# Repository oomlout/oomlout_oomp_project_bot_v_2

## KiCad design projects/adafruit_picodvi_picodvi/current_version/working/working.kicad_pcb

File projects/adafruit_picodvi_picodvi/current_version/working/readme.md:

# picodvi
 
## summary 
* id: adafruit_picodvi_picodvi
* user: adafruit
* name: picodvi
* board: picodvi
* repo: https://github.com/adafruit/PicoDVI
* src_file_repo_kicad_pcb: hardware/mini_board/picodvi.kicad_pcb
* src_file_repo_kicad_pcb_link: https://github.com/adafruit/PicoDVI/tree/master/hardware/mini_board/picodvi.kicad_pcb
* src_file_repo_kicad_sch: hardware/mini_board/picodvi.kicad_sch
* src_file_repo_kicad_sch_link: https://github.com/adafruit/PicoDVI/tree/master/hardware/mini_board/picodvi.kicad_sch

* src_file_repo_sch: hardware/mini_board/picodvi.sch
* src_file_repo_sch_link: https://github.com/adafruit/PicoDVI/tree/master/hardware/mini_board/picodvi.sch
* full details link: https://github.com/oomlout/oomlout_oomp_project_bot_v_2/tree/main/projects/adafruit_picodvi_picodvi/current_version/working  

## schematic  
  
[schematic (pdf)](working_schematic.pdf) 

## pcb  

[board (pdf)](working.pdf)  

## working_bom
| Id | Designator | Footprint | Quantity | Designation | Supplier and ref |  | None | 
| --- | --- | --- | --- | --- | --- | --- | --- | 
| 1 | R6,R1,R2 | R_0402_1005Metric | 3 | 2k2 |  |  | [''] | 
| 2 | D1 | LED_0805_2012Metric | 1 | LED |  |  | [''] | 
| 3 | J5 | HDMI-SS-53000 | 1 | NOT_HDMI_A |  |  | [''] | 
| 4 | TP1 | TestPoint_Pad_1.0x1.0mm | 1 | TestPoint |  |  | [''] | 
| 5 | J1 | USB_A_PLUG_PCB | 1 | USB_A |  |  | [''] | 
| 6 | U1 | QFN-56_EP_7x7_Pitch0.4mm | 1 | RP2040 |  |  | [''] | 
| 7 | C13,C6,C2,C8,C9,C5,C4 | C_0402_1005Metric | 7 | 100n |  |  | [''] | 
| 8 | R3,R12,R18,R17,R16,R19,R15,R13,R14 | R_0402_1005Metric | 9 | 270 |  |  | [''] | 
| 9 | C7,C3,C11,C1 | C_0402_1005Metric | 4 | 1u |  |  | [''] | 
| 10 | SW2,SW1 | SW_SPST_PTS815 | 2 | SW_Push |  |  | [''] | 
| 11 | Y1 | Crystal_SMD_3225-4Pin_3.2x2.5mm | 1 | 12 M |  |  | [''] | 
| 12 | R4,R5 | R_0402_1005Metric | 2 | 27R |  |  | [''] | 
| 13 | U2 | SOT-23-5_HandSoldering | 1 | NCP115ASN330 |  |  | [''] | 
| 14 | C10,C12 | C_0402_1005Metric | 2 | 10p |  |  | [''] | 
| 15 | U3 | WSON-8-1EP_6x5mm_P1.27mm_EP3.4x4mm | 1 | W25Q16JV |  |  | [''] | 

## bom_schematic
| Ref | Qnty | Value | Cmp name | Footprint | Description | Vendor | DNP | 
| --- | --- | --- | --- | --- | --- | --- | --- | 
| C1, C3, C7, C11, C22, C23, C24 | 7 | 1u | C | Capacitor_SMD:C_0402_1005Metric | Unpolarized capacitor |  |  | 
| C2, C4, C5, C6, C8, C9, C13 | 7 | 100n | C | Capacitor_SMD:C_0402_1005Metric | Unpolarized capacitor |  |  | 
| C10, C12 | 2 | 10p | C | Capacitor_SMD:C_0402_1005Metric | Unpolarized capacitor |  |  | 
| D1, D2 | 2 | LED | LED | LED_SMD:LED_0805_2012Metric | Light emitting diode |  |  | 
| J1 | 1 | USB_OTG | USB_OTG-Connector | Connector_USB:USB_Micro-B_Molex-105017-0001 |  |  |  | 
| J2 | 1 | Conn_01x05 | Conn_01x05 | picodvi:PinHeader_1x05_P2.54mm_Vertical | Generic connector, single row, 01x05, script generated (kicad-library-utils/schlib/autogen/connector/) |  |  | 
| J3, J4 | 2 | 02x06 | Conn_02x06_Odd_Even | picodvi:PinHeader_2x06_P2.54mm_Horizontal | Generic connector, double row, 02x06, odd/even pin numbering scheme (row 1 odd numbers, row 2 even numbers), script generated (kicad-library-utils/schlib/autogen/connector/) |  |  | 
| J5 | 1 | NOT_HDMI_A | HDMI_A | picodvi:HDMI-SS-53000 | HDMI type A connector |  |  | 
| J6 | 1 | Conn_01x02 | Conn_01x02 | Connector_PinHeader_2.54mm:PinHeader_1x02_P2.54mm_Vertical | Generic connector, single row, 01x02, script generated (kicad-library-utils/schlib/autogen/connector/) |  |  | 
| R1, R3, R6, R7, R8, R9, R11, R20 | 8 | 2k2 | R | Resistor_SMD:R_0402_1005Metric | Resistor |  |  | 
| R2 | 1 | DNF | R | Resistor_SMD:R_0402_1005Metric | Resistor |  |  | 
| R4, R5 | 2 | 27R | R | Resistor_SMD:R_0402_1005Metric | Resistor |  |  | 
| R10, R12, R13, R14, R15, R16, R17, R18, R19 | 9 | 270 | R | Resistor_SMD:R_0402_1005Metric | Resistor |  |  | 
| SW1, SW2, SW3 | 3 | SW_Push | SW_Push | picodvi:SW_SPST_PTS815 | Push button switch, generic, two pins |  |  | 
| U1 | 1 | RP2040 | Pico2040 | picodvi:QFN-56_EP_7x7_Pitch0.4mm |  |  |  | 
| U2 | 1 | NCP115ASN330 | NCP115ASN330 | Package_TO_SOT_SMD:SOT-23-5_HandSoldering |  |  |  | 
| U3 | 1 | W25Q16JV | AT25SF081-XMHD-X-Memory_Flash | Package_SON:WSON-8-1EP_6x5mm_P1.27mm_EP3.4x4mm |  |  |  | 
| Y1 | 1 | 12 M | Crystal_GND24 | Crystal:Crystal_SMD_3225-4Pin_3.2x2.5mm | Four pin crystal, GND on pins 2 and 4 |  |  |

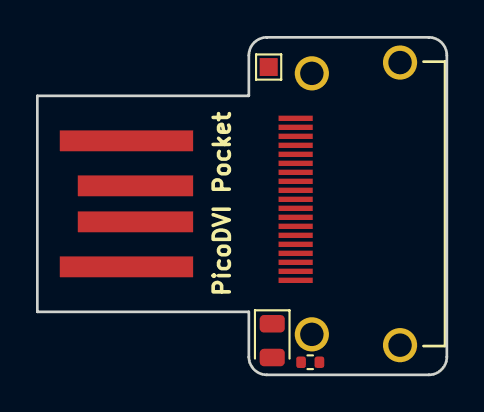
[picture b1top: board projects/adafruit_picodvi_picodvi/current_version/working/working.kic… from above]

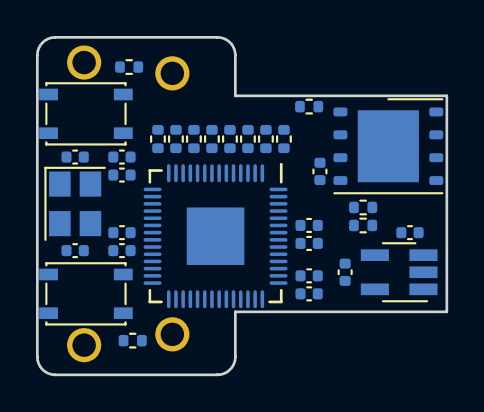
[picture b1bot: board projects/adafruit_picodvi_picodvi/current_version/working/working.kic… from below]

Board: 4 copper layers, 22.8 x 18.8 mm, 37 parts (32 on the bottom side), 37 nets, no tracks yet.

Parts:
C1, C3, C7, C11: 1u; C_0402_1005Metric
C2, C4, C5, C6, C8, C9, C13: 100n; C_0402_1005Metric
C10, C12: 10p; C_0402_1005Metric
D1: LED; LED_0805_2012Metric
J1: USB_A; USB_A_PLUG_PCB
J5: NOT_HDMI_A; HDMI-SS-53000
R1, R2, R6: 2k2; R_0402_1005Metric
R3, R12, R13, R14, R15, R16, R17, R18, R19: 270; R_0402_1005Metric
R4, R5: 27R; R_0402_1005Metric
SW1, SW2: SW_Push; SW_SPST_PTS815
TP1: TestPoint; TestPoint_Pad_1.0x1.0mm
U1: RP2040; QFN-56_EP_7x7_Pitch0.4mm
U2: NCP115ASN330; SOT-23-5_HandSoldering
U3: W25Q16JV; WSON-8-1EP_6x5mm_P1.27mm_EP3.4x4mm
Y1: 12 M; Crystal_SMD_3225-4Pin_3.2x2.5mm

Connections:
+1V1: C3.1, C5.1, C8.1, U1.23 (DVDD), U1.45 (LDO_VOUT), U1.50 (DVDD)
+3V3: C1.1, C2.1, C4.1, C6.1, C9.1, C11.1, C13.1, R1.1, R2.1, U1.1 (IOVDD), U1.10 (IOVDD), U1.22 (IOVDD), U1.33 (IOVDD), U1.42 (IOVDD), U1.43 (ADC_IOVDD), U1.44 (LDO_IOVDD), U1.48 (USB_IOVDD), U1.49 (IOVDD), U2.5 (OUT), U3.8 (VCC)
/DVI_CK+: J5.10 (CK+), R15.1
/DVI_CK-: J5.12 (CK-), R19.1
/DVI_D0+: J5.7 (D0+), R14.1
/DVI_D0-: J5.9 (D0-), R18.1
/DVI_D1+: J5.4 (D1+), R13.1
/DVI_D1-: J5.6 (D1-), R17.1
/DVI_D2+: J5.1 (D2+), R12.1
/DVI_D2-: J5.3 (D2-), R16.1
/FLASH_SCK: U1.52 (QSPI_SCK), U3.6 (SCK)
/FLASH_SD0: U1.53 (QSPI_SD0), U3.5 (SI/IO0)
/FLASH_SD1: U1.55 (QSPI_SD1), U3.2 (SO/IO1)
/FLASH_SD2: U1.54 (QSPI_SD2), U3.3 (~WP~/IO2)
/FLASH_SD3: U1.51 (QSPI_SD3), U3.7 (~HOLD~/IO3)
/FLASH_~CS: R3.1, U1.56 (~QSPI_SS~), U3.1 (~CS)
/RUN_~RST: R1.2, SW1.2, U1.26 (RUN/~RST~)
/SPARE_IO: TP1.1, U1.40 (ADC2/GPIO28)
/USB_D+: J1.3 (D+), R5.1
/USB_D-: J1.2 (D-), R4.1
/USB_DX+: R5.2, U1.47 (USB_DP)
/USB_DX-: R4.2, U1.46 (USB_DM)
/USER_LED: R6.1, U1.18 (GPIO15), U1.39 (ADC1/GPIO27)
/XIN: C12.1, U1.20 (XIN), Y1.3
/XOUT: C10.1, U1.21 (XOUT), Y1.1
/uC_DVI_CK+: R15.2, U1.7 (GPIO5)
/uC_DVI_CK-: R19.2, U1.6 (GPIO4)
/uC_DVI_D0+: R14.2, U1.9 (GPIO7)
/uC_DVI_D0-: R18.2, U1.8 (GPIO6)
/uC_DVI_D1+: R13.2, U1.12 (GPIO9)
/uC_DVI_D1-: R17.2, U1.11 (GPIO8)
/uC_DVI_D2+: R12.2, U1.14 (GPIO11)
/uC_DVI_D2-: R16.2, U1.13 (GPIO10)
/~USER_BUTTON: R2.2, R3.2, SW2.2, U1.17 (GPIO14)
GND: C1.2, C2.2, C3.2, C4.2, C5.2, C6.2, C7.2, C8.2, C9.2, C10.2, C11.2, C12.2, C13.2, D1.1 (K), J1.4 (GND), J5.2 (D2S), J5.5 (D1S), J5.8 (D0S), J5.11 (CKS), J5.17 (GND), J5.SH, SW1.1, SW2.1, U1.0 (GND), U1.19 (TESTEN), U2.2 (GND), U3.4 (GND), Y1.2, Y1.4
unnamed: D1.2 (A), R6.2
VBUS: C7.1, J1.1 (VBUS), J5.18 (+5V), U2.1 (IN), U2.3 (EN)

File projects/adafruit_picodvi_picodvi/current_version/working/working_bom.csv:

"Id";"Designator";"Footprint";"Quantity";"Designation";"Supplier and ref";
1;"R6,R1,R2";"R_0402_1005Metric";3;"2k2";;;
2;"D1";"LED_0805_2012Metric";1;"LED";;;
3;"J5";"HDMI-SS-53000";1;"NOT_HDMI_A";;;
4;"TP1";"TestPoint_Pad_1.0x1.0mm";1;"TestPoint";;;
5;"J1";"USB_A_PLUG_PCB";1;"USB_A";;;
6;"U1";"QFN-56_EP_7x7_Pitch0.4mm";1;"RP2040";;;
7;"C13,C6,C2,C8,C9,C5,C4";"C_0402_1005Metric";7;"100n";;;
8;"R3,R12,R18,R17,R16,R19,R15,R13,R14";"R_0402_1005Metric";9;"270";;;
9;"C7,C3,C11,C1";"C_0402_1005Metric";4;"1u";;;
10;"SW2,SW1";"SW_SPST_PTS815";2;"SW_Push";;;
11;"Y1";"Crystal_SMD_3225-4Pin_3.2x2.5mm";1;"12 M";;;
12;"R4,R5";"R_0402_1005Metric";2;"27R";;;
13;"U2";"SOT-23-5_HandSoldering";1;"NCP115ASN330";;;
14;"C10,C12";"C_0402_1005Metric";2;"10p";;;
15;"U3";"WSON-8-1EP_6x5mm_P1.27mm_EP3.4x4mm";1;"W25Q16JV";;;

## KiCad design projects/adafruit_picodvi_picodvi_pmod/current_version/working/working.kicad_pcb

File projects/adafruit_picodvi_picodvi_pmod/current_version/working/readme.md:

# picodvi
 
## summary 
* id: adafruit_picodvi_picodvi_pmod
* user: adafruit
* name: picodvi
* board: picodvi_pmod
* repo: https://github.com/adafruit/PicoDVI
* src_file_repo_kicad_pcb: hardware/pmod_hdmi/picodvi_pmod.kicad_pcb
* src_file_repo_kicad_pcb_link: https://github.com/adafruit/PicoDVI/tree/master/hardware/pmod_hdmi/picodvi_pmod.kicad_pcb
* src_file_repo_kicad_sch: hardware/mini_board/picodvi.kicad_sch
* src_file_repo_kicad_sch_link: https://github.com/adafruit/PicoDVI/tree/master/hardware/mini_board/picodvi.kicad_sch

* src_file_repo_sch: hardware/pmod_hdmi/picodvi_pmod.sch
* src_file_repo_sch_link: https://github.com/adafruit/PicoDVI/tree/master/hardware/pmod_hdmi/picodvi_pmod.sch
* full details link: https://github.com/oomlout/oomlout_oomp_project_bot_v_2/tree/main/projects/adafruit_picodvi_picodvi_pmod/current_version/working  

## schematic  
  
[schematic (pdf)](working_schematic.pdf) 

## pcb  

[board (pdf)](working.pdf)  

## working_bom
| Id | Designator | Footprint | Quantity | Designation | Supplier and ref |  | None | 
| --- | --- | --- | --- | --- | --- | --- | --- | 
| 1 | C2,C3,C4,C5,C6,C7,C8,C9,C1 | C_0402_1005Metric | 9 | 220n |  |  | [''] | 
| 2 | J2 | PinHeader_1x02_P2.54mm_Vertical | 1 | Conn_01x02 |  |  | [''] | 
| 3 | J1 | PinSocket_2x06_P2.54mm_Horizontal | 1 | 02x06 |  |  | [''] | 
| 4 | J3 | HDMI-SS-53000 | 1 | HDMI_A |  |  | [''] | 

## bom_schematic
| Ref | Qnty | Value | Cmp name | Footprint | Description | Vendor | DNP | 
| --- | --- | --- | --- | --- | --- | --- | --- | 
| C1, C2, C3, C4, C5, C6, C7, C8, C9 | 9 | 220n | C | Capacitor_SMD:C_0402_1005Metric | Unpolarized capacitor |  |  | 
| J1 | 1 | 02x06 | Conn_02x06_Odd_Even | Connector_PinSocket_2.54mm:PinSocket_2x06_P2.54mm_Horizontal | Generic connector, double row, 02x06, odd/even pin numbering scheme (row 1 odd numbers, row 2 even numbers), script generated (kicad-library-utils/schlib/autogen/connector/) |  |  | 
| J2 | 1 | Conn_01x02 | Conn_01x02 | Connector_PinHeader_2.54mm:PinHeader_1x02_P2.54mm_Vertical | Generic connector, single row, 01x02, script generated (kicad-library-utils/schlib/autogen/connector/) |  |  | 
| J3 | 1 | HDMI_A | HDMI_A | picodvi:HDMI-SS-53000 | HDMI type A connector |  |  |

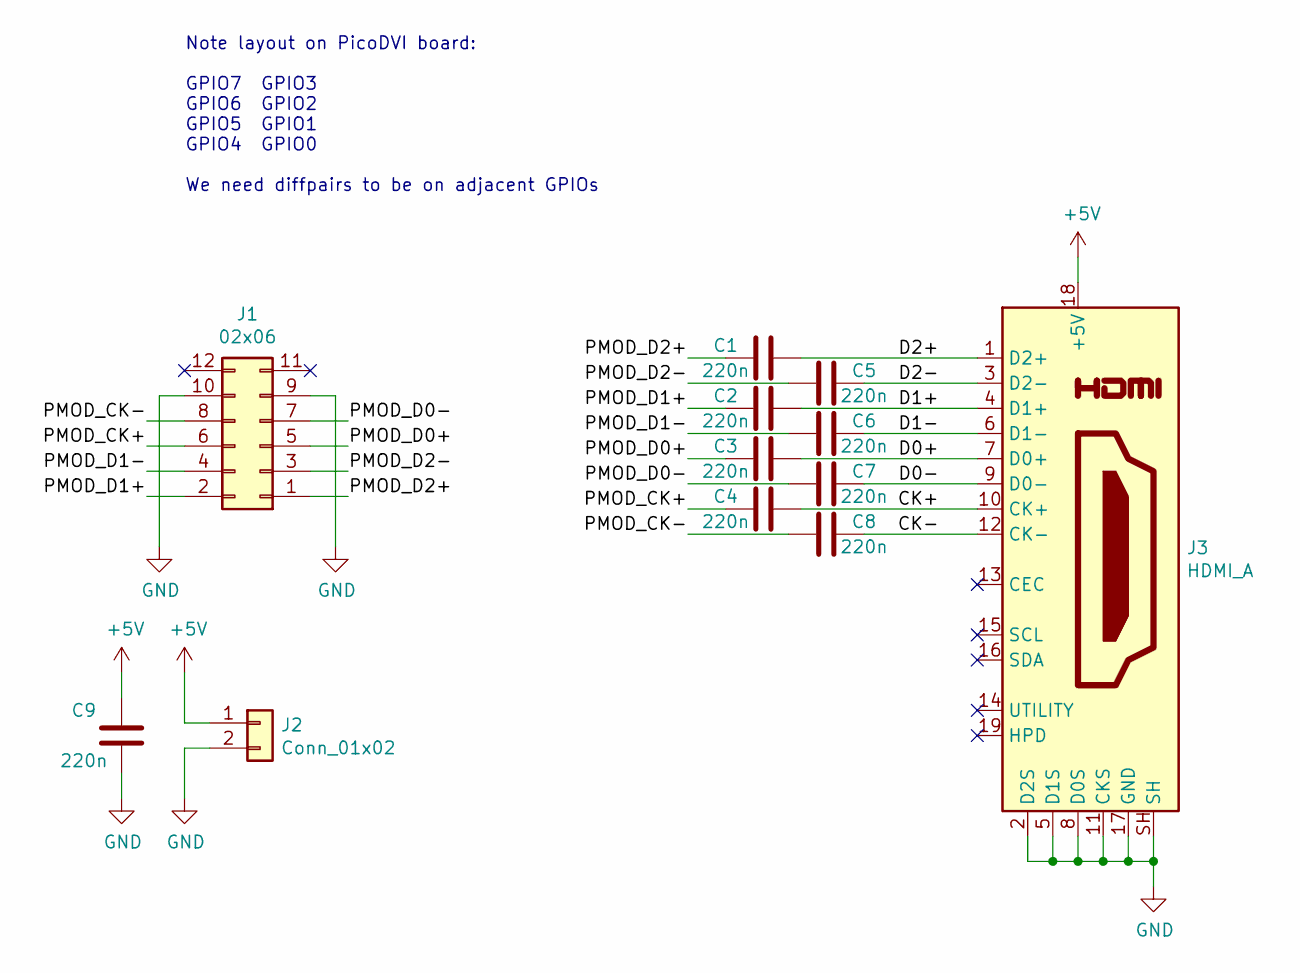
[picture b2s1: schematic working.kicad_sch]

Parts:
C1, C2, C3, C4, C5, C6, C7, C8, C9: 220n; C_0402_1005Metric
J1: 02x06; PinSocket_2x06_P2.54mm_Horizontal
J2: Conn_01x02; PinHeader_1x02_P2.54mm_Vertical
J3: HDMI_A; HDMI-SS-53000

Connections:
+3V3: J1.11, J1.12
+5V: C9.2, J2.1, J3.18 (+5V)
/CK+: C4.1, J3.10 (CK+)
/CK-: C8.1, J3.12 (CK-)
/D0+: C3.1, J3.7 (D0+)
/D0-: C7.1, J3.9 (D0-)
/D1+: C2.1, J3.4 (D1+)
/D1-: C6.1, J3.6 (D1-)
/D2+: C1.1, J3.1 (D2+)
/D2-: C5.1, J3.3 (D2-)
/PMOD_CK+: C4.2, J1.6
/PMOD_CK-: C8.2, J1.8
/PMOD_D0+: C3.2, J1.5
/PMOD_D0-: C7.2, J1.7
/PMOD_D1+: C2.2, J1.2
/PMOD_D1-: C6.2, J1.4
/PMOD_D2+: C1.2, J1.1
/PMOD_D2-: C5.2, J1.3
GND: C9.1, J1.9, J1.10, J2.2, J3.2 (D2S), J3.5 (D1S), J3.8 (D0S), J3.11 (CKS), J3.17 (GND), J3.SH

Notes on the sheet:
Note layout on PicoDVI board: GPIO7 GPIO3 GPIO6 GPIO2 GPIO5 GPIO1 GPIO4 GPIO0 We need diffpairs to be on adjacent GPIOs

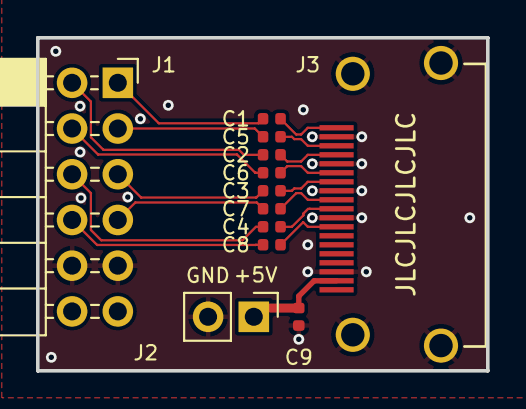
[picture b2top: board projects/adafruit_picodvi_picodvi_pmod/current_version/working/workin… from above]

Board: 2 copper layers, 25.0 x 18.5 mm, 12 parts (0 on the bottom side), 19 nets.

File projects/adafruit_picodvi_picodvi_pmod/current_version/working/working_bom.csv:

"Id";"Designator";"Footprint";"Quantity";"Designation";"Supplier and ref";
1;"C2,C3,C4,C5,C6,C7,C8,C9,C1";"C_0402_1005Metric";9;"220n";;;
2;"J2";"PinHeader_1x02_P2.54mm_Vertical";1;"Conn_01x02";;;
3;"J1";"PinSocket_2x06_P2.54mm_Horizontal";1;"02x06";;;
4;"J3";"HDMI-SS-53000";1;"HDMI_A";;;

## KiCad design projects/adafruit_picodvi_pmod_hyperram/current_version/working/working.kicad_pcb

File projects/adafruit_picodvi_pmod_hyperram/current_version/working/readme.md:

# picodvi
 
## summary 
* id: adafruit_picodvi_pmod_hyperram
* user: adafruit
* name: picodvi
* board: pmod_hyperram
* repo: https://github.com/adafruit/PicoDVI
* src_file_repo_kicad_pcb: hardware/pmod_hyperram/pmod_hyperram.kicad_pcb
* src_file_repo_kicad_pcb_link: https://github.com/adafruit/PicoDVI/tree/master/hardware/pmod_hyperram/pmod_hyperram.kicad_pcb
* src_file_repo_kicad_sch: hardware/mini_board/picodvi.kicad_sch
* src_file_repo_kicad_sch_link: https://github.com/adafruit/PicoDVI/tree/master/hardware/mini_board/picodvi.kicad_sch

* src_file_repo_sch: hardware/pmod_hyperram/pmod_hyperram.sch
* src_file_repo_sch_link: https://github.com/adafruit/PicoDVI/tree/master/hardware/pmod_hyperram/pmod_hyperram.sch
* full details link: https://github.com/oomlout/oomlout_oomp_project_bot_v_2/tree/main/projects/adafruit_picodvi_pmod_hyperram/current_version/working  

## schematic  
  
[schematic (pdf)](working_schematic.pdf) 

## pcb  

[board (pdf)](working.pdf)  

## working_bom
| Id | Designator | Footprint | Quantity | Designation | Supplier and ref |  | None | 
| --- | --- | --- | --- | --- | --- | --- | --- | 
| 1 | C2,C3,C1 | C_0402_1005Metric | 3 | 100n |  |  | [''] | 
| 2 | J1,J2 | PinSocket_2x06_P2.54mm_Horizontal | 2 | 2.54mm_2x6 |  |  | [''] | 
| 3 | R1 | R_0402_1005Metric | 1 | 4k7 |  |  | [''] | 
| 4 | U1 | S70KS128 | 1 | S70KS128 |  |  | [''] | 

## bom_schematic
| Ref | Qnty | Value | Cmp name | Footprint | Description | Vendor | DNP | 
| --- | --- | --- | --- | --- | --- | --- | --- | 
| C1, C2, C3 | 3 | 100n | C | Capacitor_SMD:C_0402_1005Metric | Unpolarized capacitor |  |  | 
| J1, J2 | 2 | 2.54mm_2x6 | Conn_02x06_Odd_Even | Connector_PinSocket_2.54mm:PinSocket_2x06_P2.54mm_Horizontal | Generic connector, double row, 02x06, odd/even pin numbering scheme (row 1 odd numbers, row 2 even numbers), script generated (kicad-library-utils/schlib/autogen/connector/) |  |  | 
| R1 | 1 | 4k7 | R | Resistor_SMD:R_0402_1005Metric | Resistor |  |  | 
| U1 | 1 | S70KS128 | S70KS128 | picodvi:S70KS128 |  |  |  |

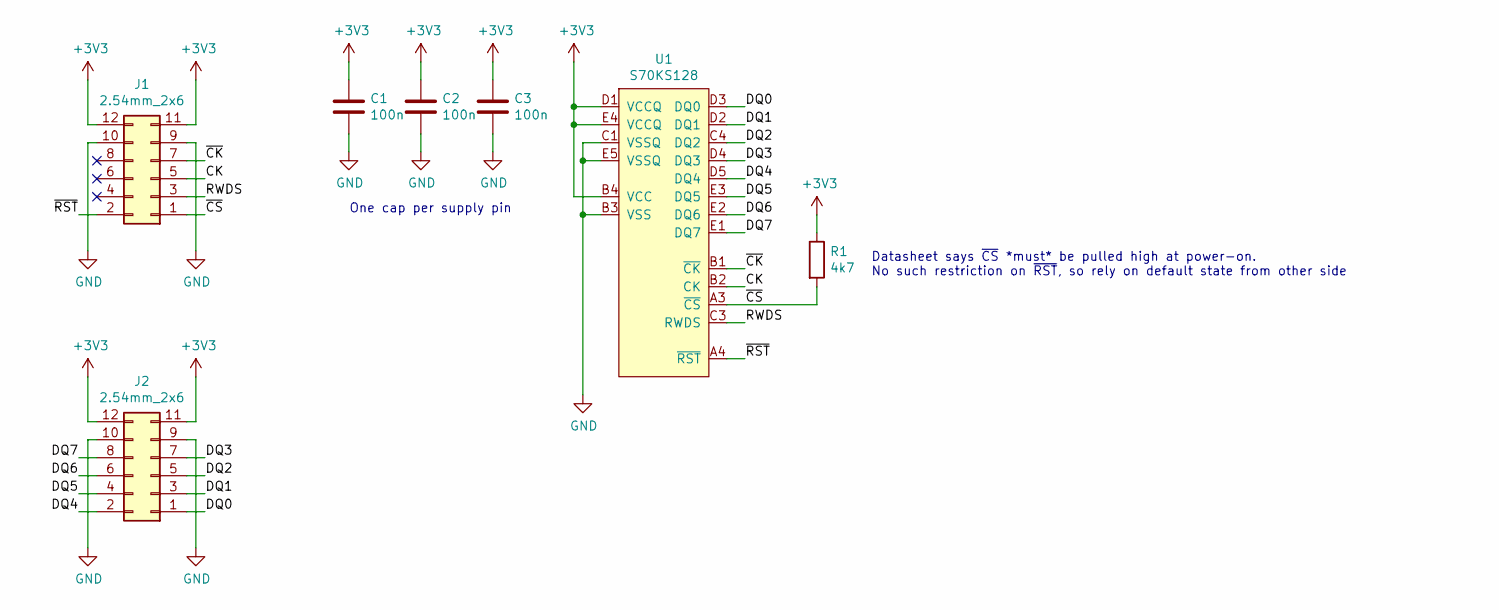
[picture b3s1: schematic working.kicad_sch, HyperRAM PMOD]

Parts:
C1, C2, C3: 100n; C_0402_1005Metric
J1, J2: 2.54mm_2x6; PinSocket_2x06_P2.54mm_Horizontal
R1: 4k7; R_0402_1005Metric
U1: S70KS128

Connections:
+3V3: C1.1, C2.1, C3.1, J1.11, J1.12, J2.11, J2.12, R1.1, U1.B4 (VCC), U1.D1 (VCCQ), U1.E4 (VCCQ)
/CK: J1.5, U1.B2 (CK)
/DQ0: J2.1, U1.D3 (DQ0)
/DQ1: J2.3, U1.D2 (DQ1)
/DQ2: J2.5, U1.C4 (DQ2)
/DQ3: J2.7, U1.D4 (DQ3)
/DQ4: J2.2, U1.D5 (DQ4)
/DQ5: J2.4, U1.E3 (DQ5)
/DQ6: J2.6, U1.E2 (DQ6)
/DQ7: J2.8, U1.E1 (DQ7)
/RWDS: J1.3, U1.C3 (RWDS)
/~CK: J1.7, U1.B1 (~CK)
/~CS: J1.1, R1.2, U1.A3 (~CS)
/~RST: J1.2, U1.A4 (~RST)
GND: C1.2, C2.2, C3.2, J1.9, J1.10, J2.9, J2.10, U1.B3 (VSS), U1.C1 (VSSQ), U1.E5 (VSSQ)

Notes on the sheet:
Datasheet says ~{CS} *must* be pulled high at power-on. No such restriction on ~{RST}, so rely on default state from other side
One cap per supply pin

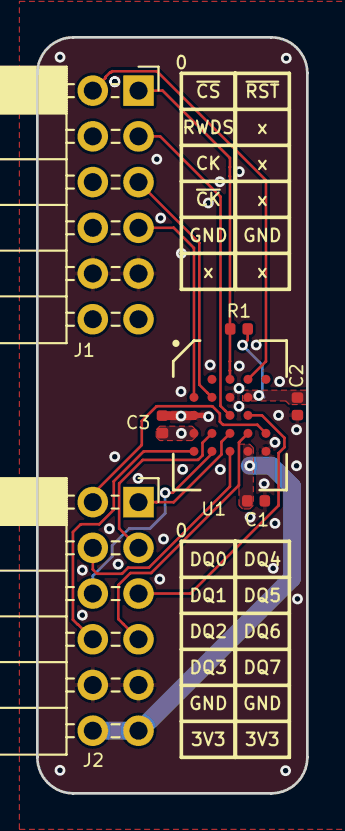
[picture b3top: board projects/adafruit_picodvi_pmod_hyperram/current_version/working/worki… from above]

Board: 2 copper layers, 15.0 x 42.0 mm, 7 parts (0 on the bottom side), 15 nets.

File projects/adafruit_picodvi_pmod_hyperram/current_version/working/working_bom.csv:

"Id";"Designator";"Footprint";"Quantity";"Designation";"Supplier and ref";
1;"C2,C3,C1";"C_0402_1005Metric";3;"100n";;;
2;"J1,J2";"PinSocket_2x06_P2.54mm_Horizontal";2;"2.54mm_2x6";;;
3;"R1";"R_0402_1005Metric";1;"4k7";;;
4;"U1";"S70KS128";1;"S70KS128";;;

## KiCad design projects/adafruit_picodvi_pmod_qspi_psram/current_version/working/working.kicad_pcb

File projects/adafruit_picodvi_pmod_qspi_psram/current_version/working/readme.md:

# picodvi
 
## summary 
* id: adafruit_picodvi_pmod_qspi_psram
* user: adafruit
* name: picodvi
* board: pmod_qspi_psram
* repo: https://github.com/adafruit/PicoDVI
* src_file_repo_kicad_pcb: hardware/pmod_qspi_psram/pmod_qspi_psram.kicad_pcb
* src_file_repo_kicad_pcb_link: https://github.com/adafruit/PicoDVI/tree/master/hardware/pmod_qspi_psram/pmod_qspi_psram.kicad_pcb
* src_file_repo_kicad_sch: hardware/mini_board/picodvi.kicad_sch
* src_file_repo_kicad_sch_link: https://github.com/adafruit/PicoDVI/tree/master/hardware/mini_board/picodvi.kicad_sch

* src_file_repo_sch: hardware/pmod_qspi_psram/pmod_qspi_psram.sch
* src_file_repo_sch_link: https://github.com/adafruit/PicoDVI/tree/master/hardware/pmod_qspi_psram/pmod_qspi_psram.sch
* full details link: https://github.com/oomlout/oomlout_oomp_project_bot_v_2/tree/main/projects/adafruit_picodvi_pmod_qspi_psram/current_version/working  

## schematic  
  
[schematic (pdf)](working_schematic.pdf) 

## pcb  

[board (pdf)](working.pdf)  

## working_bom
| Id | Designator | Footprint | Quantity | Designation | Supplier and ref |  | None | 
| --- | --- | --- | --- | --- | --- | --- | --- | 
| 1 | J1 | PinSocket_2x06_P2.54mm_Horizontal | 1 | 2.54mm_2x06 |  |  | [''] | 
| 2 | J3 | PinHeader_1x02_P2.54mm_Vertical | 1 | Conn_01x02 |  |  | [''] | 
| 3 | SW1,SW2 | SW_SPST_PTS815 | 2 | SW_Push |  |  | [''] | 
| 4 | U1 | SOIC-8_3.9x4.9mm_P1.27mm | 1 | LY68L6400 |  |  | [''] | 
| 5 | C1 | C_0402_1005Metric | 1 | 100n |  |  | [''] | 
| 6 | J2 | PinHeader_1x06_P2.54mm_Vertical | 1 | Conn_01x06 |  |  | [''] | 

## bom_schematic
| Ref | Qnty | Value | Cmp name | Footprint | Description | Vendor | DNP | 
| --- | --- | --- | --- | --- | --- | --- | --- | 
| C1 | 1 | 100n | C | Capacitor_SMD:C_0402_1005Metric | Unpolarized capacitor |  |  | 
| J1 | 1 | 2.54mm_2x06 | Conn_02x06_Odd_Even | Connector_PinSocket_2.54mm:PinSocket_2x06_P2.54mm_Horizontal | Generic connector, double row, 02x06, odd/even pin numbering scheme (row 1 odd numbers, row 2 even numbers), script generated (kicad-library-utils/schlib/autogen/connector/) |  |  | 
| J2 | 1 | Conn_01x06 | Conn_01x06 | Connector_PinHeader_2.54mm:PinHeader_1x06_P2.54mm_Vertical | Generic connector, single row, 01x06, script generated (kicad-library-utils/schlib/autogen/connector/) |  |  | 
| J3 | 1 | Conn_01x02 | Conn_01x02 | Connector_PinHeader_2.54mm:PinHeader_1x02_P2.54mm_Vertical | Generic connector, single row, 01x02, script generated (kicad-library-utils/schlib/autogen/connector/) |  |  | 
| SW1, SW2 | 2 | SW_Push | SW_Push | picodvi:SW_SPST_PTS815 | Push button switch, generic, two pins |  |  | 
| U1 | 1 | LY68L6400 | AT25SF081-XMHF-X-Memory_Flash | Package_SO:SOIC-8_3.9x4.9mm_P1.27mm |  |  |  |

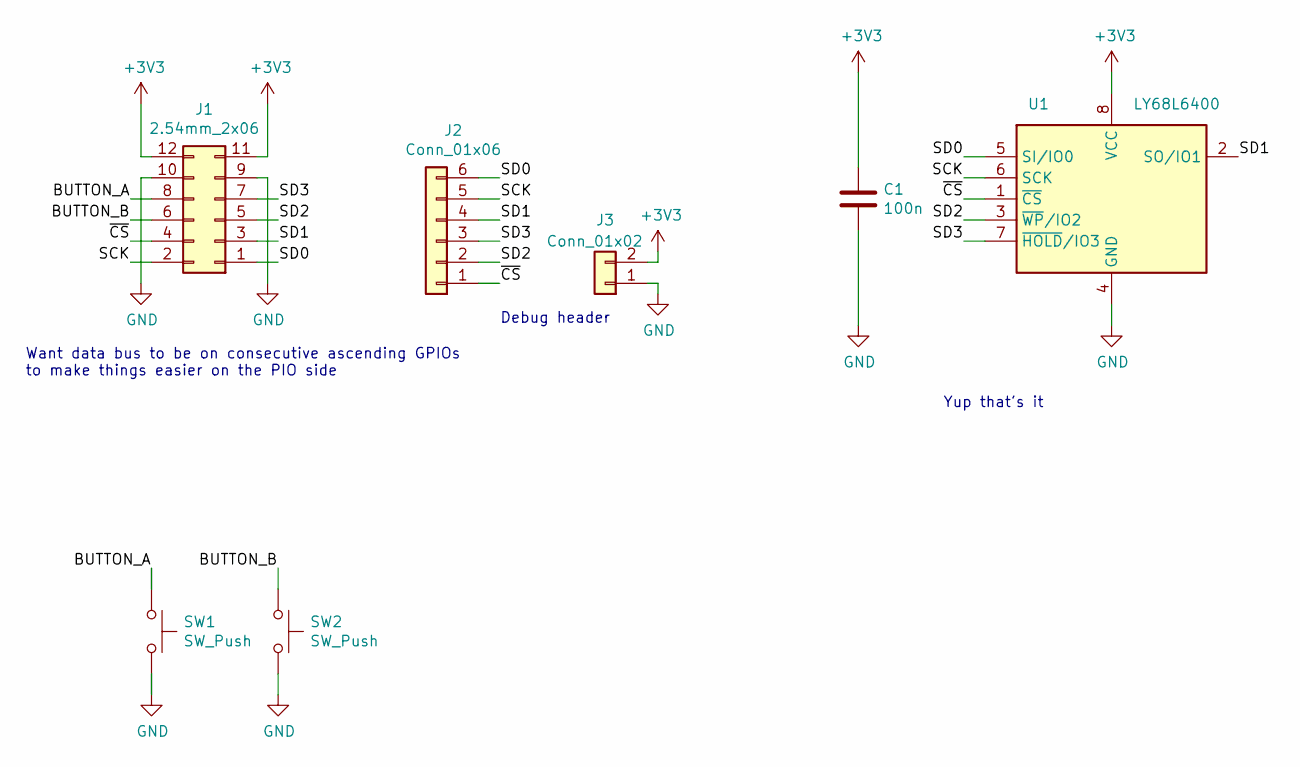
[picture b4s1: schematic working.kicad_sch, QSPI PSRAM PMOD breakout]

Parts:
C1: 100n; C_0402_1005Metric
J1: 2.54mm_2x06; PinSocket_2x06_P2.54mm_Horizontal
J2: Conn_01x06; PinHeader_1x06_P2.54mm_Vertical
J3: Conn_01x02; PinHeader_1x02_P2.54mm_Vertical
SW1, SW2: SW_Push; SW_SPST_PTS815
U1: LY68L6400; SOIC-8_3.9x4.9mm_P1.27mm

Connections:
+3V3: C1.1, J1.11, J1.12, J3.2, U1.8 (VCC)
/BUTTON_A: J1.8, SW1.1
/BUTTON_B: J1.6, SW2.1
/SCK: J1.2, J2.5, U1.6 (SCK)
/SD0: J1.1, J2.6, U1.5 (SI/IO0)
/SD1: J1.3, J2.4, U1.2 (SO/IO1)
/SD2: J1.5, J2.2, U1.3 (~WP/IO2)
/SD3: J1.7, J2.3, U1.7 (~HOLD/IO3)
/~CS: J1.4, J2.1, U1.1 (~CS)
GND: C1.2, J1.9, J1.10, J3.1, SW1.2, SW2.2, U1.4 (GND)

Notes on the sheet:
Debug header
Yup that's it
Want data bus to be on consecutive ascending GPIOs to make things easier on the PIO side

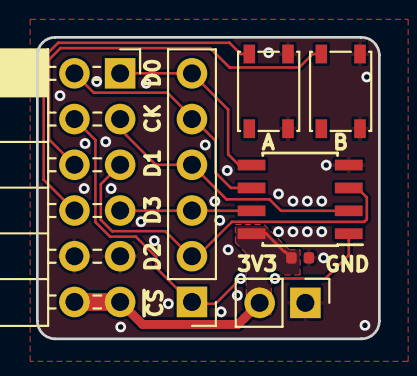
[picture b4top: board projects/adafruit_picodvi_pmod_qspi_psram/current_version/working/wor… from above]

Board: 2 copper layers, 19.0 x 16.8 mm, 7 parts (0 on the bottom side), 10 nets.

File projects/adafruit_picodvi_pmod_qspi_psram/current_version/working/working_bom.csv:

"Id";"Designator";"Footprint";"Quantity";"Designation";"Supplier and ref";
1;"J1";"PinSocket_2x06_P2.54mm_Horizontal";1;"2.54mm_2x06";;;
2;"J3";"PinHeader_1x02_P2.54mm_Vertical";1;"Conn_01x02";;;
3;"SW1,SW2";"SW_SPST_PTS815";2;"SW_Push";;;
4;"U1";"SOIC-8_3.9x4.9mm_P1.27mm";1;"LY68L6400";;;
5;"C1";"C_0402_1005Metric";1;"100n";;;
6;"J2";"PinHeader_1x06_P2.54mm_Vertical";1;"Conn_01x06";;;

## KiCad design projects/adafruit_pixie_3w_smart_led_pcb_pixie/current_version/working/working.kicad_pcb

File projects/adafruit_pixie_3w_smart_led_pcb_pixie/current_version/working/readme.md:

# pixie_3w_smart_led_pcb
 
## summary 
* id: adafruit_pixie_3w_smart_led_pcb_pixie
* user: adafruit
* name: pixie_3w_smart_led_pcb
* board: pixie
* repo: https://github.com/adafruit/Pixie-3W-Smart-LED-PCB

* src_file_repo_sch: 
* src_file_repo_sch_link: https://github.com/adafruit/Pixie-3W-Smart-LED-PCB/tree/master/
* full details link: https://github.com/oomlout/oomlout_oomp_project_bot_v_2/tree/main/projects/adafruit_pixie_3w_smart_led_pcb_pixie/current_version/working  

## schematic  
  
[schematic (pdf)](working_schematic.pdf) 

## pcb  

[board (pdf)](working.pdf)  

## working_bom
| Id | Designator | Footprint | Quantity | Designation | Supplier and ref |  | None | 
| --- | --- | --- | --- | --- | --- | --- | --- | 
| 1 | R9 | _0603MP | 1 | 100 |  |  | [''] | 
| 2 | !MCLR0,PGC0,PGD0 | PAD.03X.04 | 3 | TEST-POINT3X4 |  |  | [''] | 
| 3 | U$4,U$3,U$1,U$2 | ALIGN_CROSS | 4 | ALIGN_CROSS |  |  | [''] | 
| 4 | R4,R6,R2 | 0603-RES | 3 | 47k |  |  | [''] | 
| 5 | Q3,Q5,Q1 | SOT23-3 | 3 | IRLML2060TRPBF |  |  | [''] | 
| 6 | R5,R3,R1 | 1206 | 3 | 1.74 0.25W |  |  | [''] | 
| 7 | IN0,OUT0 | 1X03-0.1PWR+SIG | 2 |  |  |  | [''] | 
| 8 | R8 | 0603-RES | 1 | 33 |  |  | [''] | 
| 9 | U$6,U$7 | FIDUCIAL_1MM | 2 | FIDUCIAL" |  |  | [''] | 
| 10 | @HOLE0,@HOLE1 |  | 2 |  |  |  | [''] | 
| 11 | C2,C1 | _0805MP | 2 | 22uF,6.3V |  |  | [''] | 
| 12 | IC1 | MSOP-8 | 1 | PIC12(L)F157X |  |  | [''] | 
| 13 | R7 | 0603-RES | 1 | 100 |  |  | [''] | 
| 14 | Q2,Q6,Q4 | SOT23-3 | 3 | MMBT2222A |  |  | [''] | 
| 15 | U$8 | PCBFEAT-REV-040 | 1 |  |  |  | [''] | 
| 16 | LED1 | RGBLED3W4PIN | 1 | RGBLED_CA |  |  | [''] | 
| 17 | U$5 | PIXIE-LOGO | 1 | PIXIE-LOGO |  |  | [''] | 

## bom_schematic
| Ref | Qnty | Value | Cmp name | Footprint | Description | Vendor | DNP | 
| --- | --- | --- | --- | --- | --- | --- | --- | 
| !MCLR0 | 1 | TEST-POINT3X4 | TEST-POINT3X4 | working:PAD.03X.04 |  |  |  | 
| C1, C2 | 2 | 22uF,6.3V | CAP_CERAMIC_0805MP | working:_0805MP |  |  |  | 
| IC1 | 1 | PIC12(L)F157X | PIC12(L)F157X | working:MSOP-8 |  |  |  | 
| IN0 | 1 | M030.1PWR+SIG | M030.1PWR+SIG | working:1X03-0.1PWR+SIG |  |  |  | 
| LED1 | 1 | RGBLED_CA | RGBLED_CA | working:RGBLED3W4PIN |  |  |  | 
| OUT0 | 1 | M030.1PWR+SIG | M030.1PWR+SIG | working:1X03-0.1PWR+SIG |  |  |  | 
| PGC0 | 1 | TEST-POINT3X4 | TEST-POINT3X4 | working:PAD.03X.04 |  |  |  | 
| PGD0 | 1 | TEST-POINT3X4 | TEST-POINT3X4 | working:PAD.03X.04 |  |  |  | 
| Q1, Q3, Q5 | 3 | IRLML2060TRPBF | IRLML2060TRPBF | working:SOT23-3 |  |  |  | 
| Q2, Q4, Q6 | 3 | MMBT2222A | MMBT2222A | working:SOT23-3 |  |  |  | 
| R1, R3, R5 | 3 | 1.74 0.25W | RESISTOR1206 | working:1206 |  |  |  | 
| R2, R4, R6 | 3 | 47k | RGBLED_RESISTOR0603 | working:0603-RES |  |  |  | 
| R7 | 1 | 100 | RGBLED_RESISTOR0603 | working:0603-RES |  |  |  | 
| R8 | 1 | 33 | RGBLED_RESISTOR0603 | working:0603-RES |  |  |  | 
| R9 | 1 | 100 | RESISTOR_0603MP | working:_0603MP |  |  |  | 
| U$1, U$2, U$3, U$4 | 4 | ALIGN_CROSS | ALIGN_CROSS | working:ALIGN_CROSS |  |  |  | 
| U$5 | 1 | PIXIE-LOGO | PIXIE-LOGO | working:PIXIE-LOGO |  |  |  | 
| U$6, U$7 | 2 | FIDUCIAL"" | FIDUCIAL{dblquote}{dblquote} | working:FIDUCIAL_1MM |  |  |  |

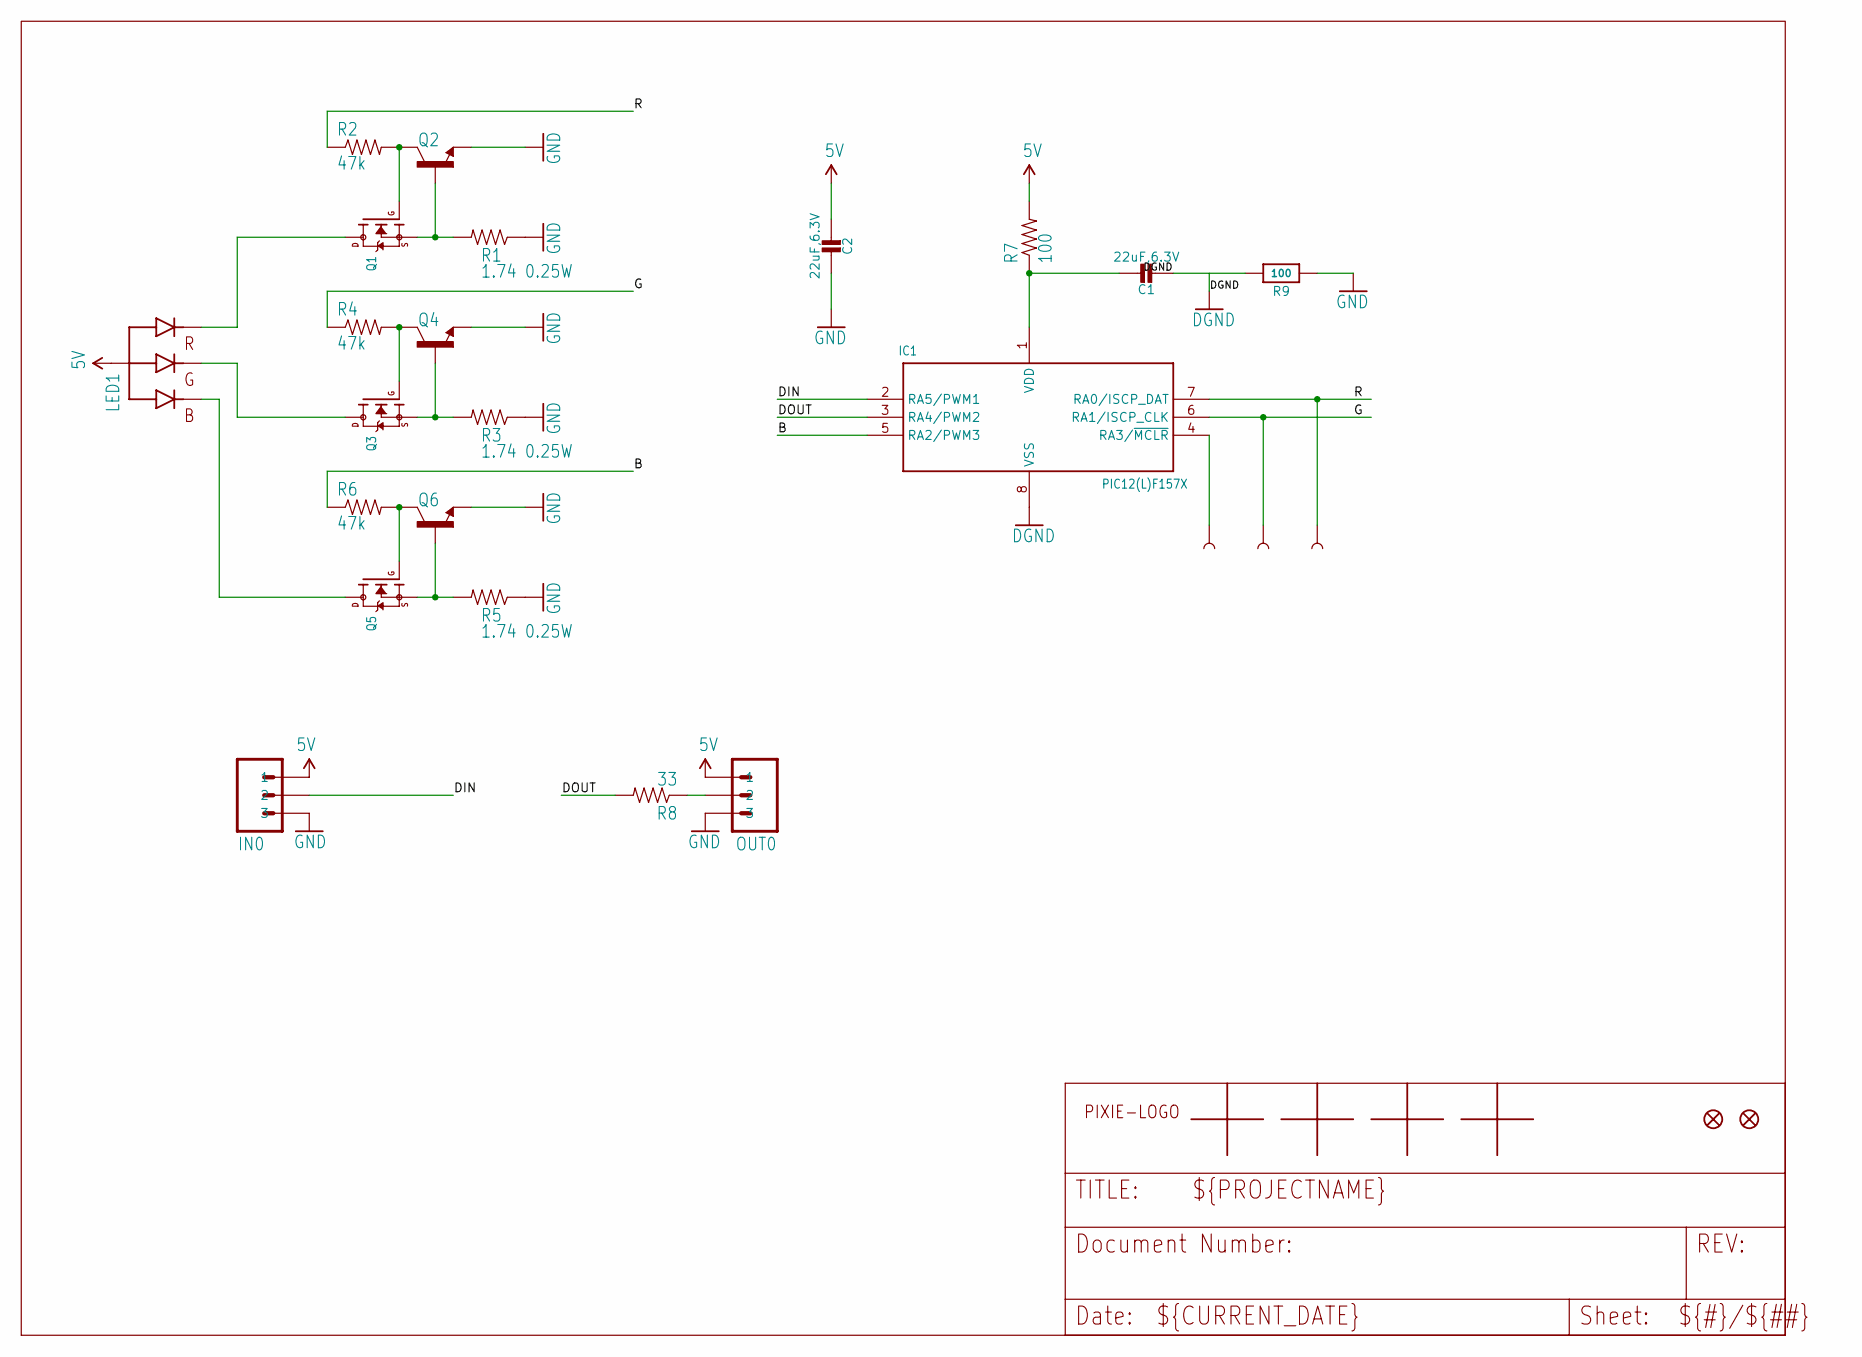
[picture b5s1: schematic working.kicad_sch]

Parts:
!MCLR0: TEST-POINT3X4; PAD.03X.04
C1, C2: 22uF,6.3V; _0805MP
IC1: PIC12(L)F157X; MSOP-8
IN0: M030.1PWR+SIG; 1X03-0.1PWR+SIG
LED1: RGBLED_CA; RGBLED3W4PIN
OUT0: M030.1PWR+SIG; 1X03-0.1PWR+SIG
PGC0: TEST-POINT3X4; PAD.03X.04
PGD0: TEST-POINT3X4; PAD.03X.04
Q1, Q3, Q5: IRLML2060TRPBF; SOT23-3
Q2, Q4, Q6: MMBT2222A; SOT23-3
R1, R3, R5: 1.74 0.25W; 1206
R2, R4, R6: 47k; 0603-RES
R7: 100; 0603-RES
R8: 33; 0603-RES
R9: 100; _0603MP
U$1, U$2, U$3, U$4: ALIGN_CROSS
U$5: PIXIE-LOGO
U$6, U$7: FIDUCIAL""; FIDUCIAL_1MM

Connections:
5V: C2.2, IN0.P$1 (1), LED1.ANODE (VCC), OUT0.P$1 (1), R7.2
B: IC1.5 (RA2/PWM3), R6.1
DGND: C1.2, IC1.8 (VSS), R9.2
DIN: IC1.2 (RA5/PWM1), IN0.P$2 (2)
DOUT: IC1.3 (RA4/PWM2), R8.2
G: IC1.6 (RA1/ISCP_CLK), PGC0.P$1, R4.1
GND: C2.1, IN0.P$3 (3), OUT0.P$3 (3), Q2.2 (E), Q4.2 (E), Q6.2 (E), R1.1, R3.1, R5.1, R9.1
unnamed: LED1.R (RED), Q1.3 (D)
unnamed: LED1.G (GREEN), Q3.3 (D)
unnamed: LED1.B (BLUE), Q5.3 (D)
unnamed: Q1.2 (S), Q2.1 (B), R1.2
unnamed: Q3.2 (S), Q4.1 (B), R3.2
unnamed: OUT0.P$2 (2), R8.1
unnamed: !MCLR0.P$1, IC1.4 (RA3/~MCLR)
unnamed: Q5.1 (G), Q6.3 (C), R6.2
unnamed: Q3.1 (G), Q4.3 (C), R4.2
unnamed: C1.1, IC1.1 (VDD), R7.1
unnamed: Q5.2 (S), Q6.1 (B), R5.2
unnamed: Q1.1 (G), Q2.3 (C), R2.2
R: IC1.7 (RA0/ISCP_DAT), PGD0.P$1, R2.1

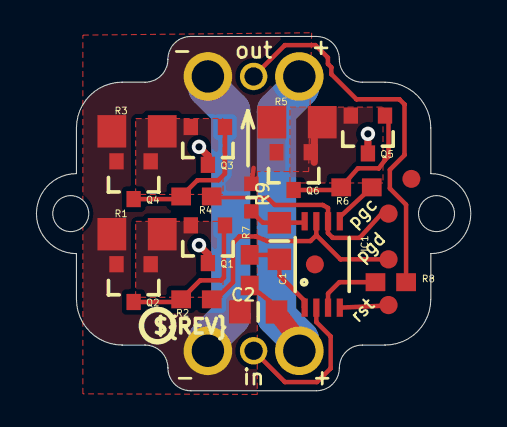
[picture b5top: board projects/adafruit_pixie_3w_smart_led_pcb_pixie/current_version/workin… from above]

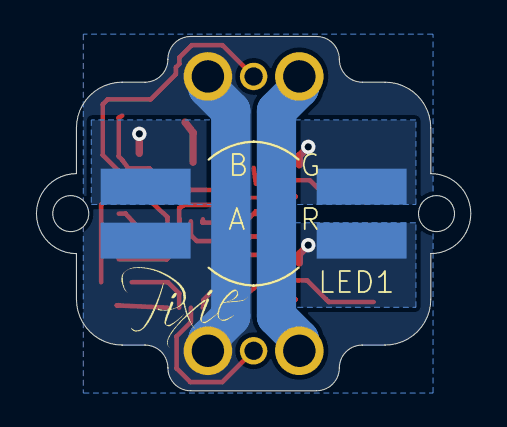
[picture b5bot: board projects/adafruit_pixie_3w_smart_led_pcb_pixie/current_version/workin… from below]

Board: 16 copper layers, 24.1 x 19.7 mm, 34 parts (2 on the bottom side), 20 nets.

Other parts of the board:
@HOLE0, @HOLE1: (no value)
U$8: PCBFEAT-REV-040

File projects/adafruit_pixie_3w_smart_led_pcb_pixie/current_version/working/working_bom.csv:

"Id";"Designator";"Footprint";"Quantity";"Designation";"Supplier and ref";
1;"R9";"_0603MP";1;"100";;;
2;"!MCLR0,PGC0,PGD0";"PAD.03X.04";3;"TEST-POINT3X4";;;
3;"U$4,U$3,U$1,U$2";"ALIGN_CROSS";4;"ALIGN_CROSS";;;
4;"R4,R6,R2";"0603-RES";3;"47k";;;
5;"Q3,Q5,Q1";"SOT23-3";3;"IRLML2060TRPBF";;;
6;"R5,R3,R1";"1206";3;"1.74 0.25W";;;
7;"IN0,OUT0";"1X03-0.1PWR+SIG";2;"";;;
8;"R8";"0603-RES";1;"33";;;
9;"U$6,U$7";"FIDUCIAL_1MM";2;"FIDUCIAL""";;;
10;"@HOLE0,@HOLE1";"";2;"";;;
11;"C2,C1";"_0805MP";2;"22uF,6.3V";;;
12;"IC1";"MSOP-8";1;"PIC12(L)F157X";;;
13;"R7";"0603-RES";1;"100";;;
14;"Q2,Q6,Q4";"SOT23-3";3;"MMBT2222A";;;
15;"U$8";"PCBFEAT-REV-040";1;"";;;
16;"LED1";"RGBLED3W4PIN";1;"RGBLED_CA";;;
17;"U$5";"PIXIE-LOGO";1;"PIXIE-LOGO";;;

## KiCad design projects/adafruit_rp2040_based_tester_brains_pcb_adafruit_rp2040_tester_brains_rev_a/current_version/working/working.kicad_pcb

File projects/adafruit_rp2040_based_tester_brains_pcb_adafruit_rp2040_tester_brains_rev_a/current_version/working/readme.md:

# rp2040_based_tester_brains_pcb
 
## summary 
* id: adafruit_rp2040_based_tester_brains_pcb_adafruit_rp2040_tester_brains_rev_a
* user: adafruit
* name: rp2040_based_tester_brains_pcb
* board: adafruit_rp2040_tester_brains_rev_a
* repo: https://github.com/adafruit/RP2040-Based-Tester-Brains-PCB

* src_file_repo_sch: 
* src_file_repo_sch_link: https://github.com/adafruit/RP2040-Based-Tester-Brains-PCB/tree/main/
* full details link: https://github.com/oomlout/oomlout_oomp_project_bot_v_2/tree/main/projects/adafruit_rp2040_based_tester_brains_pcb_adafruit_rp2040_tester_brains_rev_a/current_version/working  

## schematic  
  
[schematic (pdf)](working_schematic.pdf) 

## pcb  

[board (pdf)](working.pdf)  

## working_bom
| Id | Designator | Footprint | Quantity | Designation | Supplier and ref |  | None | 
| --- | --- | --- | --- | --- | --- | --- | --- | 
| 1 | C3,C9,C7,C5,C1,C4,C8,C6,C2 | 0805-NO | 9 | 10uF |  |  | [''] | 
| 2 | CB1 | PICOWBELL_DUALSMT | 1 | PICOWBELL_DUALSMT |  |  | [''] | 
| 3 | U$8,U$10,U$9,U$7 | MOUNTINGHOLE_3.0_PLATEDTHIN | 4 | MOUNTINGHOLE3.0THIN |  |  | [''] | 
| 4 | CONN1 | JST_SH4 | 1 | STEMMA_I2C_QT |  |  | [''] | 
| 5 | FID2,FID3,FID1 | FIDUCIAL_1MM | 3 | FIDUCIAL_1MM |  |  | [''] | 
| 6 | SP1 | PS12 | 1 | SPEAKER/PS12 |  |  | [''] | 
| 7 | JP1 | 2X20_SMT_MALE | 1 | 16x2 LCD |  |  | [''] | 
| 8 | R5,R1,R2,R3,R4 | 0603-NO | 5 | 10K |  |  | [''] | 
| 9 | TP2,TP4,TP3,TP1 | SMT_NUT_3MM | 4 | SEWTAP_SMTNUTM3 |  |  | [''] | 
| 10 | R6,R8,R7,R9 | 0603-NO | 4 | 27 |  |  | [''] | 
| 11 | TFT1 | TFT_1.9IN_170X320_30P_SS | 1 | DISP_LCD_ST7789_1.9IN_SS |  |  | [''] | 
| 12 | SW1 | B3F-40XX-SMT | 1 | 12mm SMT |  |  | [''] | 
| 13 | IC1 | SO08-SKINNYPADS | 1 | WS2811-SOP8 |  |  | [''] | 
| 14 | Q3,Q5,Q4 | SOT23-WIDE | 3 | BSS138 |  |  | [''] | 
| 15 | X1 | USB_HOST-SMT | 1 | USB A |  |  | [''] | 
| 16 | X3 | FPC_0.5MM_18PIN | 1 | TESTER_PROGCABLE_FLIP |  |  | [''] | 
| 17 | VR1 | TRIMPOT_BOURNS_TC33X-2 | 1 | 10K Trimmer |  |  | [''] | 
| 18 | Q2,Q1 | SOT23-WIDE | 2 | DMG34x5 |  |  | [''] | 
| 19 | X2 | MICROSD | 1 | MicroSD |  |  | [''] | 
| 20 | U$13 | PCBFEAT-REV-040 | 1 |  |  |  | [''] | 
| 21 | JP8 | 1X12_OVAL | 1 |  |  |  | [''] | 
| 22 | SW2 | EG1390 | 1 | DPDT SLIDE |  |  | [''] | 

## bom_schematic
| Ref | Qnty | Value | Cmp name | Footprint | Description | Vendor | DNP | 
| --- | --- | --- | --- | --- | --- | --- | --- | 
| C1, C2, C3, C4, C5, C6, C7, C8, C9 | 9 | 10uF | CAP_CERAMIC0805-NOOUTLINE | working:0805-NO |  |  |  | 
| CB1 | 1 | PICOWBELL_DUALSMT | PICOWBELL_DUALSMT | working:PICOWBELL_DUALSMT |  |  |  | 
| CONN1 | 1 | STEMMA_I2C_QT | STEMMA_I2C_QT | working:JST_SH4 |  |  |  | 
| FID1, FID2, FID3 | 3 | FIDUCIAL_1MM | FIDUCIAL_1MM | working:FIDUCIAL_1MM |  |  |  | 
| IC1 | 1 | WS2811-SOP8 | WS2811-SOP8 | working:SO08-SKINNYPADS |  |  |  | 
| JP1 | 1 | 16x2 LCD | PINHD-2X20_SMT | working:2X20_SMT_MALE |  |  |  | 
| JP8 | 1 | HEADER-1X12OVAL | HEADER-1X12OVAL | working:1X12_OVAL |  |  |  | 
| Q1, Q2 | 2 | DMG34x5 | MOSFET-PWIDE | working:SOT23-WIDE |  |  |  | 
| Q3, Q4, Q5 | 3 | BSS138 | MOSFET-NWIDE | working:SOT23-WIDE |  |  |  | 
| R1, R2, R3, R4, R5 | 5 | 10K | RESISTOR_0603_NOOUT | working:0603-NO |  |  |  | 
| R6, R7, R8, R9 | 4 | 27 | RESISTOR_0603_NOOUT | working:0603-NO |  |  |  | 
| SP1 | 1 | SPEAKER/PS12 | SPEAKER/PS12 | working:PS12 |  |  |  | 
| SW1 | 1 | 12mm SMT | SWITCH_TACT_SMT_12MM | working:B3F-40XX-SMT |  |  |  | 
| SW2 | 1 | DPDT SLIDE | SWITCH_DPDTEG1390 | working:EG1390 |  |  |  | 
| TFT1 | 1 | DISP_LCD_ST7789_1.9IN_SS | DISP_LCD_ST7789_1.9IN_SS | working:TFT_1.9IN_170X320_30P_SS |  |  |  | 
| TP1, TP2, TP3, TP4 | 4 | SEWTAP_SMTNUTM3 | SEWTAP_SMTNUTM3 | working:SMT_NUT_3MM |  |  |  | 
| U$7, U$8, U$9, U$10 | 4 | MOUNTINGHOLE3.0THIN | MOUNTINGHOLE3.0THIN | working:MOUNTINGHOLE_3.0_PLATEDTHIN |  |  |  | 
| VR1 | 1 | 10K Trimmer | TRIMPOTTC33X-2 | working:TRIMPOT_BOURNS_TC33X-2 |  |  |  | 
| X1 | 1 | USB A | USB_TYPEA_SMT | working:USB_HOST-SMT |  |  |  | 
| X2 | 1 | MicroSD | MICROSD | working:MICROSD |  |  |  | 
| X3 | 1 | TESTER_PROGCABLE_FLIP | TESTER_PROGCABLE_FLIP | working:FPC_0.5MM_18PIN |  |  |  | 

## mounting_holes
| x | y | package | value | ref | size | 
| --- | --- | --- | --- | --- | --- | 
| 97.66 | 63.5 | MOUNTINGHOLE_3.0_PLATEDTHIN | MOUNTINGHOLE3.0THIN | U$7 | m3 | 
| 0.0 | 63.63 | MOUNTINGHOLE_3.0_PLATEDTHIN | MOUNTINGHOLE3.0THIN | U$8 | m3 | 
| 0.0 | 0.13 | MOUNTINGHOLE_3.0_PLATEDTHIN | MOUNTINGHOLE3.0THIN | U$9 | m3 | 
| 97.66 | 0.0 | MOUNTINGHOLE_3.0_PLATEDTHIN | MOUNTINGHOLE3.0THIN | U$10 | m3 |

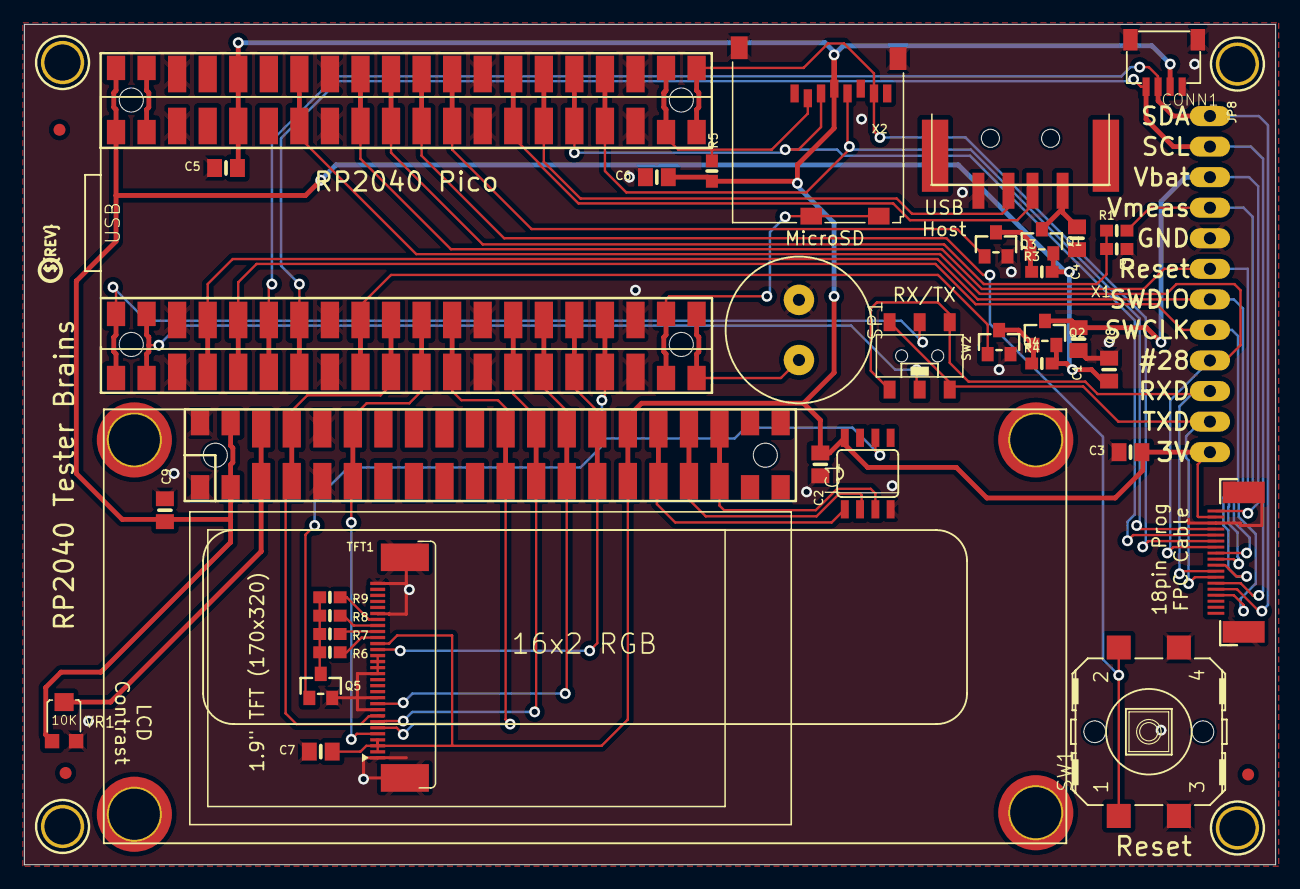
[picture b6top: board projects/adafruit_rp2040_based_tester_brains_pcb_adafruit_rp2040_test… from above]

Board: 2 copper layers, 104.0 x 69.8 mm, 48 parts (0 on the bottom side), 47 nets.

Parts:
C1, C2, C3, C4, C5, C6, C7, C8, C9: 10uF; 0805-NO
CB1: PICOWBELL_DUALSMT
CONN1: STEMMA_I2C_QT; JST_SH4
FID1, FID2, FID3: FIDUCIAL_1MM
IC1: WS2811-SOP8; SO08-SKINNYPADS
JP1: 16x2 LCD; 2X20_SMT_MALE
JP8: 1X12_OVAL
Q1, Q2: DMG34x5; SOT23-WIDE
Q3, Q4, Q5: BSS138; SOT23-WIDE
R1, R2, R3, R4, R5: 10K; 0603-NO
R6, R7, R8, R9: 27; 0603-NO
SP1: SPEAKER/PS12; PS12
SW1: 12mm SMT; B3F-40XX-SMT
SW2: DPDT SLIDE; EG1390
TFT1: DISP_LCD_ST7789_1.9IN_SS; TFT_1.9IN_170X320_30P_SS
TP1, TP2, TP3, TP4: SEWTAP_SMTNUTM3; SMT_NUT_3MM
U$7, U$8, U$9, U$10: MOUNTINGHOLE3.0THIN; MOUNTINGHOLE_3.0_PLATEDTHIN
U$13: PCBFEAT-REV-040
VR1: 10K Trimmer; TRIMPOT_BOURNS_TC33X-2
X1: USB A; USB_HOST-SMT
X2: MicroSD; MICROSD
X3: TESTER_PROGCABLE_FLIP; FPC_0.5MM_18PIN

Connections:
3.3V: C2.1, C3.1, C5.1, C6.1, C7.1, CB1.S71, CB1.S72, CONN1.2, IC1.8, JP1.29, JP1.30, JP8.12, R5.1, TFT1.2, TFT1.3, TFT1.4, TFT1.20, X2.4, X3.2
+5V: C8.1, C9.1, CB1.S79, CB1.S80, JP1.3, JP1.4, Q1.2, Q2.2, R3.2, R4.2, VR1.1
GND: C1.2, C2.2, C3.2, C4.2, C5.2, C6.2, C7.2, C8.2, C9.2, CB1.S5, CB1.S6, CB1.S15, CB1.S16, CB1.S25, CB1.S26, CB1.S35, CB1.S36, CB1.S45, CB1.S46, CB1.S55, CB1.S56, CB1.S65, CB1.S66, CB1.S75, CB1.S76, CONN1.1, CONN1.MT1, CONN1.MT2, IC1.4, JP1.1, JP1.2, JP1.9, JP1.10, JP8.5, Q3.2, Q4.2, Q5.2, R2.1, SP1.P$1, SW1.P$3, SW1.P$4, TFT1.1, TFT1.9, TFT1.11, TFT1.12, TFT1.13, TFT1.14, TFT1.15, TFT1.16, TFT1.17, TFT1.18, TFT1.25, TFT1.30, TFT1.MNT1, TFT1.MNT2, TP1.P$1, TP2.P$1, TP3.P$1, TP4.P$1, VR1.3, X1.GND, X2.6, X2.MT1, X2.MT2, X3.3, X3.SUPPORT1, X3.SUPPORT2
GPIO28: CB1.S67, CB1.S68, JP8.9, X3.7
LCD_BLUE: IC1.3, JP1.35, JP1.36
LCD_D4: CB1.S23, CB1.S24, JP1.21, JP1.22, TFT1.6
LCD_D5: CB1.S27, CB1.S28, JP1.23, JP1.24, TFT1.7
LCD_D6: CB1.S29, CB1.S30, JP1.25, JP1.26, TFT1.10
LCD_D7: CB1.S31, CB1.S32, JP1.27, JP1.28, TFT1.19
LCD_E: CB1.S21, CB1.S22, JP1.11, JP1.12, TFT1.5
LCD_GREEN: IC1.2, JP1.33, JP1.34
LCD_NEO: CB1.S33, CB1.S34, IC1.6, Q5.1
LCD_RED: IC1.1, JP1.31, JP1.32
LCD_RS: CB1.S19, CB1.S20, JP1.7, JP1.8, TFT1.8
LEDK: Q5.3, R6.1, R7.1, R8.1, R9.1
MISO: CB1.S41, CB1.S42, X2.7, X3.6
MOSI: CB1.S49, CB1.S50, X2.3, X3.5
unnamed: CB1.S39, CB1.S40, SP1.P$2
unnamed: R6.2, TFT1.21
unnamed: R7.2, TFT1.22
unnamed: R8.2, TFT1.23
unnamed: R9.2, TFT1.24
unnamed: JP1.5, JP1.6, VR1.2
RESET: CB1.S59, CB1.S60, SW1.P$1, SW1.P$2
RXD: CB1.S3, CB1.S4, SW2.P1
RXI: JP8.10, SW2.O2, SW2.S1, X3.11
SCK: CB1.S47, CB1.S48, X2.5, X3.4
SCL: CB1.S13, CB1.S14, CONN1.4, JP8.2, X3.13
SDA: CB1.S11, CB1.S12, CONN1.3, JP8.1, X3.14
SD_CD: CB1.S37, CB1.S38, X2.CD1, X2.CD2
SD_CS: CB1.S43, CB1.S44, R5.2, X2.2
SWCLK: CB1.S9, CB1.S10, JP8.8, X3.10
SWDIO: CB1.S7, CB1.S8, JP8.7, X3.9
TARGET_RESET: CB1.S63, CB1.S64, JP8.6, X3.8
TXD: CB1.S1, CB1.S2, SW2.P2
TXO: JP8.11, SW2.O1, SW2.S2, X3.12
USB_D+: CB1.S51, CB1.S52, X1.D+
USB_D-: CB1.S53, CB1.S54, X1.D-
VBAT: C1.1, JP8.3, Q2.3, X3.1
VBAT_SW: CB1.S17, CB1.S18, Q4.1
VMEAS: JP8.4, R1.2, X3.15
VMEAS_DIV2: CB1.S61, CB1.S62, R1.1, R2.2
VSYS: CB1.S77, CB1.S78
VUSB: C4.1, Q1.3, X1.VBUS
VUSB_SW: CB1.S57, CB1.S58, Q3.1
~VBAT_SW1: Q2.1, Q4.3, R4.1
~VBAT_SW2: Q1.1, Q3.3, R3.1
